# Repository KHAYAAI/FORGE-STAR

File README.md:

# FORGE STAR

**Africa's sovereign satellite data network.** Locally owned low-Earth-orbit (LEO) infrastructure that connects the assets, vessels and people that terrestrial networks will never reach. Data is landed and hosted in South Africa.

FORGE STAR starts with satellite IoT, maritime AIS and sovereign data relay, not consumer broadband. It runs as a ground and services company first (revenue before orbit), then becomes a satellite operator. It's part of the FORGE ecosystem (MYFORGE PTY LTD).

> All figures are illustrative. Regulatory, market and vendor facts need confirming before external use (see [`docs/verification/VERIFY.md`](docs/verification/VERIFY.md)). Not financial advice.

---

## Start here: documents

| Document | For | What it is |
|---|---|---|
| **[Technical and investor brief (PDF)](output/FORGE_STAR_Brief.pdf)** | Investors, counsel, engineers, partners, due diligence | One brief with a section for each reader: case, market, financials, regulation, architecture, RF design, flight software, ground platform, hardware plan, evidence, path to launch, risks, where FORGE STAR reaches (global coverage map, first export markets), sources |
| [Strategy (PDF)](output/FORGE_STAR_Strategy.pdf) · [source](docs/strategy.md) | Founders, board | The full strategy with every analysis check |
| [Launch readiness](docs/LAUNCH_READINESS.md) | Everyone | Scorecard, TRL, critical path, blockers (generated) |
| [Verification register](docs/verification/VERIFY.md) | Counsel, engineers | Every claim, vendor figure and radio value still to confirm, with sources |
| [ITU filing parameters](docs/itu/FILING_PARAMETERS.md) | Spectrum counsel | Draft NGSO filing sheet generated from the design |
| [Mission operations](docs/operations/mission-ops.md) · [Security and POPIA](docs/operations/security.md) | Operations, security | Procedures and controls |

Both PDFs are built from markdown in `docs/`:

```bash
python3 scripts/build_pdf.py                                        # strategy
python3 scripts/build_pdf.py --src docs/brief.md --out output/FORGE_STAR_Brief.pdf \
  --subtitle "Technical and investor brief" --label "Brief v1.2  ·  November 2026  ·  Confidential"
```

---

## The platform in one picture

```mermaid
flowchart LR
    subgraph Field["In the field"]
        D["Devices<br/>mine pumps, farm sensors,<br/>collars, vessels, trackers"]
    end
    subgraph Space["Space segment"]
        S["FORGE STAR satellites<br/>F´ flight software + libforge<br/>store-and-forward buffer"]
    end
    subgraph Ground["Ground segment (SA)"]
        G["Gateways<br/>Hartebeesthoek, Cape Town + partners<br/>FEC decode, dedupe, acks"]
        K[("Kafka")]
        DB[("TimescaleDB<br/>hosted in SA")]
    end
    subgraph Customers["Customers"]
        TB["ThingsBoard<br/>dashboards"]
        API["Customer API<br/>devices, messages, SLA, usage"]
    end
    R["Resale partner<br/>(Stage 0, before our satellites)"]

    D -- "NB-IoT NTN uplink<br/>(re-sent until acked)" --> S
    S -- "X-band downlink<br/>RS(255,223) CCSDS" --> G
    G -- "ACK frames" --> S
    S -. "acks relayed" .-> D
    D -. "Stage 0" .-> R --> K
    G --> K --> DB
    DB --> TB
    DB --> API
```

**How a message travels:**
1. A device sends a reading. Every FORGE STAR satellite overhead takes a copy and holds it on board.
2. When a satellite passes over a gateway, it sends its stored messages down in error-corrected link blocks.
3. The gateway decodes them, removes duplicate copies and records each message. It then sends acknowledgements back up.
4. Satellites relay the acknowledgements, so devices stop re-sending and satellites drop copies they no longer need.
5. Messages flow through Kafka into TimescaleDB, hosted in South Africa. Customers see them in ThingsBoard dashboards and through the API.

In **Stage 0**, before our own satellites fly, the same platform carries traffic from a resale partner. Customers get the same dashboards and API, then move onto our satellites with no change on their side.

---

## What's in this repository

| Layer | What it does | Where |
|---|---|---|
| **Flight software** | NASA F´ deployment (`Payload`): store-and-forward, signed-command authentication, safe mode, onboard pass prediction, persistence. Runs on x86 and 64-bit ARM. | [`flight/fprime/`](flight/fprime) |
| **Flight core** | Portable C99, no dynamic memory: store-and-forward buffer (CRC-checked, survives reboot), frames, acks, Reed–Solomon, HMAC command auth, pass predictor. Byte-identical to the ground code. | [`flight/libforge/`](flight/libforge) |
| **Device SDK** | C99 library for customer devices: queue, re-send until acked, expiry | [`flight/libforge/include/forge_device.h`](flight/libforge/include/forge_device.h) |
| **Mission operations** | Signed commanding and telemetry/event decoding for the flight software; procedures | [`ground/ops/`](ground/ops), [`docs/operations/`](docs/operations) |
| **Software modem** | BPSK receive chain from IQ samples (Doppler, timing, phase) with CCSDS convolutional coding + Viterbi | [`forgestar/modem.py`](forgestar/modem.py), [`forgestar/conv.py`](forgestar/conv.py) |
| **Billing** | Monthly invoices per active device with SLA credits | [`ground/billing/`](ground/billing) |
| **ITU filing sheet** | Draft NGSO filing parameters generated from the design | [`docs/itu/`](docs/itu) |
| **Link layer** | RS(255,223) with CCSDS parameters and dual basis, CCSDS randomiser, sync marker. Corrects up to 16 bad bytes per block. | [`forgestar/fec.py`](forgestar/fec.py) |
| **Frames** | Store-and-forward data frames and ACK frames shared by satellite and ground | [`forgestar/frames.py`](forgestar/frames.py) |
| **Gateway** | Decodes downlinks (Kafka, capture files, SatNOGS Network), removes duplicates, sends acks | [`ground/gateway/`](ground/gateway) |
| **Data platform** | Kafka → TimescaleDB, ingest, delivery-time (SLA) views | [`ground/`](ground) |
| **Dashboards** | ThingsBoard provisioning: devices plus an operations dashboard | [`ground/thingsboard/`](ground/thingsboard) |
| **Customer API** | FastAPI with per-customer keys: devices, messages, SLA, monthly usage; rate limits, audit log, metrics | [`ground/api/`](ground/api) |
| **Production deployment** | TLS, backups, no exposed data ports, required secrets | [`ground/deploy/`](ground/deploy) |
| **Simulated space segment** | Runs a constellation on a sped-up clock, so the whole platform can be tested without satellites | [`ground/sandf/`](ground/sandf) |
| **Constellation design** | Orbits with J2 (checked against SGP4), coverage, link budget, antenna options, delivery time | [`sim/`](sim), [`forgestar/`](forgestar) |
| **Hardware** | Circuit boards as code. Two boards placed and autorouted with every connection made and a clean KiCad design check: the payload interface board and an IoT test device. Written in Zener (Diode's open-source `pcb` tool) and SKiDL. Not yet reviewed by an engineer or built. | [`hardware/zener/`](hardware/zener), [`hardware/`](hardware) |
| **3D models** | Concept models of the demonstrator (6U), the operational IoT satellite (12U) and a broadband satellite, plus both boards. STEP and GLB files. | [`hardware/3d/`](hardware/3d) |
| **Capacity model** | Messages per satellite per pass, and how many devices a fleet can carry | [`forgestar/capacity.py`](forgestar/capacity.py), [`sim/capacity_study.py`](sim/capacity_study.py) |
| **Business** | Financial model (Stages 0–3, stress scenarios, monthly cash, 30% ownership check) | [`model/`](model) |
| **Readiness** | 40 outside milestones (ICASA/ITU, funding, partners, customers), TRL tracking, launch readiness report | [`readiness/`](readiness), [`docs/LAUNCH_READINESS.md`](docs/LAUNCH_READINESS.md) |
| **Strategy** | The full strategy; the PDF is built from it | [`docs/strategy.md`](docs/strategy.md), [`output/`](output) |

---

## Run it

**Prerequisites:** Docker, Python 3.11+, a C compiler. For the flight software you also need CMake and F´'s tools; for hardware, KiCad 7+.

```bash
git clone --recurse-submodules https://github.com/KHAYAAI/FORGE-STAR.git
cd FORGE-STAR
pip install -r requirements.txt
```

**The platform** (simulated devices and the Stage 3 constellation of 48 satellites and 6 gateways, gateway, database, API):

```bash
cd ground && docker compose up -d
```

Then:
- **Customer API docs:** http://localhost:8000/docs (create a key with `docker compose exec api python app.py create-key "FORGE Freight"`)
- **Delivery times:** `docker compose exec timescaledb psql -U forge -d forgestar -c "select * from latency_sla;"`
- **With ThingsBoard** (needs about 2 GB of RAM): `docker compose --profile full up -d`, then `python3 thingsboard/provision.py`, and open http://localhost:8080 (`tenant@thingsboard.org` / `tenant`)

**Flight software:**

```bash
cd flight/fprime && pip install -r fprime/requirements.txt
fprime-util generate && fprime-util build && fprime-util check     # build + unit tests
cd ../.. && python3 flight/run_payload.py                           # run it, decode its downlink on the ground
```

Command it (signed) from the ground: `python3 ground/ops/forge_ops.py --dict flight/fprime/build-artifacts/Linux/Payload/dict/PayloadTopologyDictionary.json --port 50000 --key <hex> --cmd Payload.cmdDisp.CMD_NO_OP`, then start the flight binary with `FORGE_CMD_KEY=<hex>` and `-a 127.0.0.1 -p 50000`.

For 64-bit ARM, use `fprime-util generate aarch64-linux && fprime-util build aarch64-linux`, then `python3 flight/run_payload.py --arch aarch64` (runs under QEMU).

**Analysis and documents:**

```bash
python3 sim/equatorial_study.py          # Stage 3 constellation and gateway design
python3 sim/antenna_trade.py             # payload antenna options, with gain tied to beam shape
python3 sim/capacity_study.py            # messages per pass and per device per day
python3 sim/coverage_map.py [--stage4]   # global coverage map -> docs/img/coverage-stage3.png
python3 model/financial_model.py         # financial model and stress tests
python3 scripts/launch_readiness.py      # docs/LAUNCH_READINESS.md
python3 scripts/build_pdf.py             # output/FORGE_STAR_Strategy.pdf
python3 -m pytest                        # test suite
```

CI runs all of this on every push: the Python tests and analysis, the platform image builds, the flight software (C core, F´ unit tests, native and ARM runs), and the hardware pipeline.

---

## Key numbers (illustrative)

| Item | Value |
|---|---|
| **Stage 3 constellation** | 42 satellites at 45° + 6 at 10° (48), 550 km |
| **Gateways** | Hartebeesthoek, Cape Town, Walvis Bay, Mauritius, Malindi, Lagos |
| **Delivery target (design)** | 95% of messages within 26 minutes at all 7 modelled customer sites |
| **Delivery measured (live run)** | 95% within ~40 minutes on 24 satellites with SA gateways only |
| **Year-6 revenue** | $37.5M base; $31.6M with IoT at ~$1/device; $19.5M without a government contract |
| **Equity to Stage 3** | ~$50M |
| **Delivery measured on the Stage 3 design (live run)** | 95% of satellite messages within 9 minutes |
| **Link margin** | Decodes at Eb/N0 ≈ 2.5 dB with CCSDS RS + convolutional coding |
| **First payload in orbit** | ~Feb 2029 on the fast track (hosted payload); ~May 2028 if everything runs in parallel with money up front; own satellite ~Jun 2029 |
| **Service antenna** | Isoflux, ~8 W RF: devices reach a satellite from 16° elevation. Needs ~38 W from the bus during passes (a 12U) |
| **Demonstrator antenna** | Simple patch: 47° elevation (34° with deep coverage mode). Poor coverage by design |
| **Capacity** | ~6 messages a second per NB-IoT carrier per satellite. Stage 3 carries ~1.4 messages per device per day at 330,000 devices |
| **Year-6 EBITDA** | $11.3M base (our satellites carry ~42% of IoT devices, the rest stay on the resale partner); $12.6M with a compact protocol of our own |

## Hardware: build, buy, bridge

Boards are written as code and checked with KiCad. The two current boards live in [`hardware/zener/`](hardware/zener), with fabrication files for review in each board's `fab/` folder; [heypcb.ai](https://heypcb.ai) remains an option for later boards. GitHub CI autoroutes the boards with Freerouting (`.github/workflows/route-boards.yml`). The gaps heypcb.ai does not cover are bridged with flight-heritage suppliers and mature tools: hosted-payload platforms or the bus partner for structure, thermal and integration; flight-heritage S/X-band radios; Antenna Magus and openEMS for antennas; SPENVIS and iThemba LABS (Cape Town) for radiation. Details, list prices and what still needs a quote are in section 09 of the brief and items V1–V7 of the verification register.

## Status

**Updated November 2026.** An independent review found the first antenna figures too optimistic. The link budget now ties antenna gain to beam shape, the simulations use the downlink limit, and the financial model is tied to fleet capacity.

The software and ground platform are at TRL 4–5. Everything that can be built without hardware is in place; the remaining software (payload radio base station, real drivers, bus integration) needs the lab kit and bus partner. Payload hardware, the bus partner, spectrum licensing, funding and customers are the work still ahead. See [`docs/LAUNCH_READINESS.md`](docs/LAUNCH_READINESS.md) for the scorecard, critical path and blockers.

Project context for Claude Code is in [`CLAUDE.md`](CLAUDE.md).

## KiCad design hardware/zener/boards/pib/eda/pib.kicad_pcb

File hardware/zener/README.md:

# FORGE STAR boards in Zener (trial)

A trial of [Diode's Zener language and `pcb` tool](https://github.com/diodeinc/pcb) (MIT licence) next to the
existing SKiDL pipeline in `hardware/boards/`. Boards are written as code; `pcb` checks them and produces KiCad files.

All designs here are first drafts with illustrative values. An electrical engineer must review them before fabrication.

| Board | File | What it is | Status |
|---|---|---|---|
| Payload interface board (PIB) | `boards/pib/pib.zen` | Port of the SKiDL board: MCU, CAN to the bus, radio power switch, telemetry | Builds, 35 components |
| IoT test device | `boards/iot_node/iot_node.zen` | Battery NB-IoT node with GNSS for the lab test-bed and field trials | Builds, 71 components |

## Use

```bash
curl -fsSL https://raw.githubusercontent.com/diodeinc/pcb/main/install.sh | bash   # installs pcb
cd hardware/zener
pcb build boards/pib/pib.zen                  # check the design
pcb build boards/iot_node/iot_node.zen
pcb bom --offline boards/iot_node/iot_node.zen   # parts list, nothing sent to Diode
pcb layout --no-open boards/pib/pib.zen       # KiCad board file (needs KiCad 10)
```

`pcb bom` without `--offline`, `pcb quote` and `pcb auth` send design data to Diode's servers. Do not use them
until an NDA and an export-control check are in place.

## Parts

Each board keeps its own symbols and footprints in `parts/`. Add one from the installed KiCad libraries with:

```bash
python3 tools/import_kicad_part.py boards/iot_node RF_GSM:BC66
```

## Layout

```bash
pcb layout --no-open boards/iot_node/iot_node.zen   # creates or updates the KiCad board (needs KiCad 10)
python3 tools/place.py boards/iot_node              # positions from placement.json, outline, ground pours
FREEROUTING_JAR=... python3 tools/route.py boards/iot_node   # autoroute + ground stitching (runs in GitHub CI)
```

| Board | Size | Placement | Routing |
|---|---|---|---|
| Payload interface board | 58 x 40 mm, 4 layers | Done | Done: every connection made, KiCad design check reports 0 errors |
| IoT test device | 84 x 45 mm, 4 layers | Done | Done: every connection made, KiCad design check reports 0 errors |

Both boards have four grounded M2.5 mounting holes and three fiducials.

Gerber, drill and placement files are in each board's `fab/` folder. They are for review, not yet for ordering.

3D pictures are in `docs/img/` (`pib-3d.png`, `iot_node-3d.png`) and 3D STEP files sit next to each board.
Several chips show as bare pads because KiCad's 3D model library is not installed here.

## Datasheet checks done (from public sources, November 2026)

| Item | Finding | Result in the design |
|---|---|---|
| MAX-M10S `VIO_SEL` | u-blox: connect to GND for 1.8 V, leave open for 3.3 V | Tied to GND. Correct for 1.8 V. |
| MAX-M10S supply | 1.76 V to 1.98 V in 1.8 V mode | The 1.8 V regulator's tolerance leaves little margin at the low end. Consider a tighter regulator. |
| BC66 `PWRKEY` | Thresholds are relative to VBAT; Quectel recommends an open-drain or open-collector driver | Driven by an open-collector transistor. Matches. |
| BC66 `RESET`, `PSM_EINT` | Active low | Driven the same way. The voltage domain of `PSM_EINT` was not found; the transistor makes it safe either way. |
| BC66 pin numbers | PWRKEY 7, RESET 15, PSM_EINT 19 | Match the KiCad symbol. |
| CC660D-LS (satellite module) | Same 17.7 x 15.8 x 2.0 mm LCC+LGA outline as BC66; has PWRKEY, PSM_EINT, UART, USIM, ADC; needs an external GNSS module | Outline and interfaces fit, and the board already has GNSS. **The pin-by-pin map is still unconfirmed**: Quectel's CC660D-LS hardware design manual is needed. |
| BC660K-GL (same footprint family) | No PWRKEY; adds BOOT and VIO_SEL; do not pull MAIN_RXD up to VDD_EXT | Not a drop-in for this board without changes. |

## Open items before fabrication

- **Autorouted, not reviewed.** Routing was done by Freerouting in CI (`.github/workflows/route-boards.yml`). Power traces use the default width, decoupling and RF traces are not hand-placed, and silkscreen has cosmetic warnings.
- **CC660D-LS pin map:** get the hardware design manual from Quectel and compare every pin.
- **RF:** antenna traces need 50 ohm controlled impedance; the matching network values are placeholders that need
  measurement on a network analyser.
- **Engineer review:** an electrical engineer must review schematic, placement and routing. The checks above are
  from public datasheet summaries, not a substitute for that review.

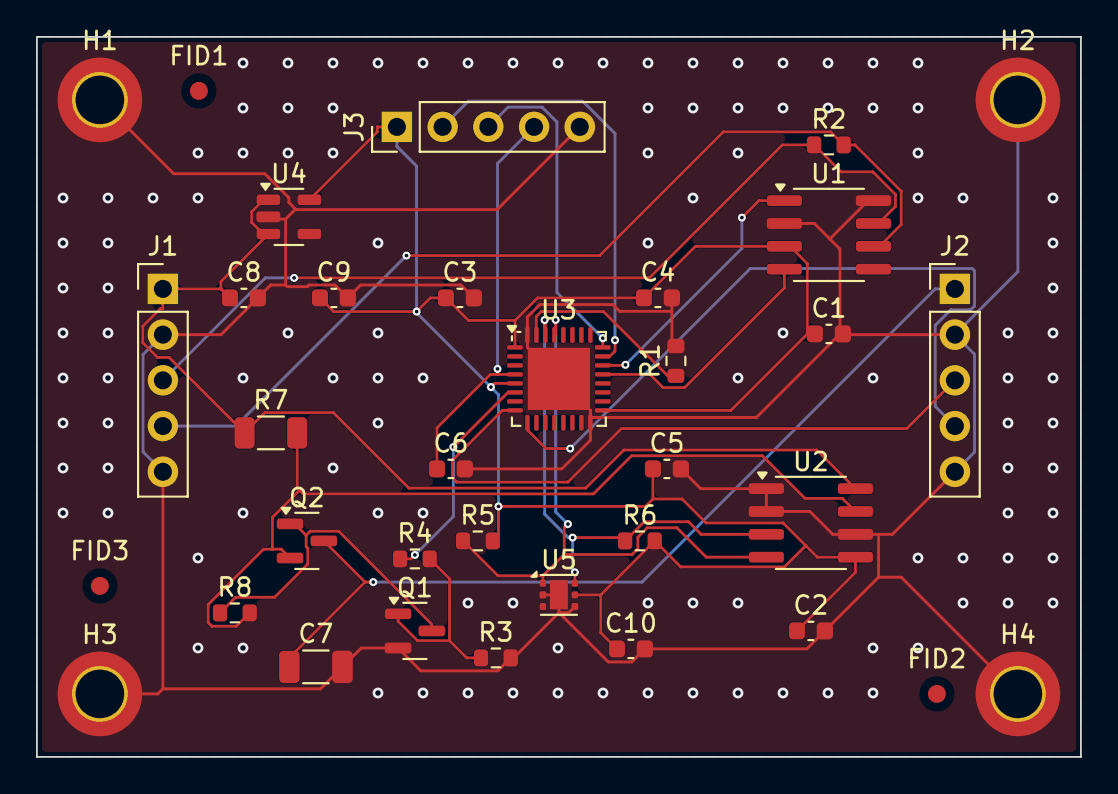
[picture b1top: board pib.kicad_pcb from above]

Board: 4 copper layers, 58.0 x 40.0 mm, 35 parts (0 on the bottom side), 20 nets.

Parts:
C1, C2, C3, C4, C10: 100nF 6.3V; C_0603_1608Metric
C5: 4.7uF 6.3V; C_0603_1608Metric
C6: 100nF; C_0603_1608Metric
C7: 10uF 10V; C_1206_3216Metric
C8: 1uF 10V; C_0603_1608Metric
C9: 1uF 6.3V; C_0603_1608Metric
FID1, FID2, FID3: Fiducial; Fiducial_1mm_Mask2mm
H1, H2, H3, H4: M2.5 DIN965 TopBottom; MountingHole_2.7mm_M2.5_DIN965_Pad_TopBottom
J1, J2, J3: 2.54mm 5 x 1 THT Vertical Male; PinHeader_1x05_P2.54mm_Vertical
Q1: 2N7002; SOT-23
Q2: AO3401A; SOT-23
R1: 10k; R_0603_1608Metric
R2: 120; R_0603_1608Metric
R3, R8: 100k; R_0603_1608Metric
R4: 100; R_0603_1608Metric
R5, R6: 4.7k; R_0603_1608Metric
R7: 50m; R_1206_3216Metric
U1: SN65HVD230DR; SOIC-8_3.9x4.9mm_P1.27mm
U2: INA219AIDR; SOIC-8_3.9x4.9mm_P1.27mm
U3: STM32L432KCU6; QFN-32-1EP_5x5mm_P0.5mm_EP3.45x3.45mm
U4: AP2112K-3.3TRG1; SOT-23-5
U5: TMP117AIDRVR; WSON-6-1EP_2x2mm_P0.65mm_EP1x1.6mm

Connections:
+3V3: C1.1, C2.1, C3.1, C4.1, C5.1, C9.1, C10.1, J3.1, R5.2, R6.2, U1.3, U2.5, U3.1, U3.5, U3.17, U4.5, U5.5
BOOT0: R1.1, U3.31
CANH: J1.3, R2.1, U1.7
CANL: J1.4, R2.2, U1.6
CAN_RX: U1.4, U3.21
CAN_TX: U1.1, U3.22
DRV_GATE: Q1.1, R3.1, R4.2
GND: C1.2, C2.2, C3.2, C4.2, C5.2, C6.2, C7.2, C8.2, C9.2, C10.2, H1.1, H2.1, H3.1, H4.1, J1.2, J1.5, J2.2, J2.5, J3.5, Q1.2, R1.2, R3.2, U1.2, U1.8, U2.1, U2.2, U2.6, U3.16, U3.32, U3.33, U4.2, U5.2, U5.4, U5.7
I2C_SCL: R5.1, U2.4, U3.29, U5.1
I2C_SDA: R6.1, U2.3, U3.30, U5.6
NRST: C6.1, J3.4, U3.4
RADIO_EN: R4.1, U3.6
RADIO_PWR: C7.1, J2.1, Q2.3
SWCLK: J3.3, U3.24
SWDIO: J3.2, U3.23
SW_GATE: Q1.3, Q2.1, R8.1
UART_RX: J2.4, U3.9
UART_TX: J2.3, U3.8
VIN: C8.1, J1.1, R7.1, U2.8, U4.1, U4.3
VIN_SENSE: Q2.2, R7.2, R8.2, U2.7

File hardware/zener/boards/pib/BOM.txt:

Legend:
 ■  Plenty available / easy to source         ■  House component       
 ■  Limited inventory / harder to source      ■  DNP (Do Not Populate) 
 ■  Insufficient stock / hard to source                                
┌──────┬─────────────────┬─────────────────┬─────────────────────────────┬─────────────────────────────────┬────────────────────────────────┐
│ Qty  ┆ Designators     ┆ MPN             ┆ Manufacturer                ┆ Package                         ┆ Description                    │
╞══════╪═════════════════╪═════════════════╪═════════════════════════════╪═════════════════════════════════╪════════════════════════════════╡
│    5 ┆ C1,C2,C3,C4,C10 ┆                 ┆                             ┆ 0603                            ┆ 100nF 6.3V                     │
│    1 ┆ C5              ┆                 ┆                             ┆ 0603                            ┆ 4.7uF 6.3V                     │
│    1 ┆ C6              ┆                 ┆                             ┆ 0603                            ┆ 100nF                          │
│    1 ┆ C7              ┆                 ┆                             ┆ 1206                            ┆ 10uF 10V                       │
│    1 ┆ C8              ┆                 ┆                             ┆ 0603                            ┆ 1uF 10V                        │
│    1 ┆ C9              ┆                 ┆                             ┆ 0603                            ┆ 1uF 6.3V                       │
│    3 ┆ J1,J2,J3        ┆                 ┆                             ┆ PinHeader_1x05_P2.54mm_Vertical ┆ 2.54mm 5 x 1 THT Vertical Male │
│    1 ┆ Q1              ┆ 2N7002          ┆ onsemi                      ┆                                 ┆                                │
│    1 ┆ Q2              ┆ AO3401A         ┆ Alpha & Omega Semiconductor ┆                                 ┆                                │
│    1 ┆ R1              ┆                 ┆                             ┆ 0603                            ┆ 10k                            │
│    1 ┆ R2              ┆                 ┆                             ┆ 0603                            ┆ 120                            │
│    2 ┆ R3,R8           ┆                 ┆                             ┆ 0603                            ┆ 100k                           │
│    1 ┆ R4              ┆                 ┆                             ┆ 0603                            ┆ 100                            │
│    2 ┆ R5,R6           ┆                 ┆                             ┆ 0603                            ┆ 4.7k                           │
│    1 ┆ R7              ┆                 ┆                             ┆ 1206                            ┆ 50m                            │
│    1 ┆ U1              ┆ SN65HVD230DR    ┆ Texas Instruments           ┆                                 ┆                                │
│    1 ┆ U2              ┆ INA219AIDR      ┆ Texas Instruments           ┆                                 ┆                                │
│    1 ┆ U3              ┆ STM32L432KCU6   ┆ STMicroelectronics          ┆                                 ┆                                │
│    1 ┆ U4              ┆ AP2112K-3.3TRG1 ┆ Diodes Incorporated         ┆                                 ┆                                │
│    1 ┆ U5              ┆ TMP117AIDRVR    ┆ Texas Instruments           ┆                                 ┆                                │
└──────┴─────────────────┴─────────────────┴─────────────────────────────┴─────────────────────────────────┴────────────────────────────────┘

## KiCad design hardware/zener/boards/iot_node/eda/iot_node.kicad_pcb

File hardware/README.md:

# FORGE STAR hardware: in-house PCB pipeline

An open-source replacement for an AI PCB service such as heypcb.ai. Boards are written as code,
checked automatically and turned into fab files on every push.

```
circuit as code (SKiDL, KiCad symbol libraries)      hardware/boards/<board>/<board>.py
   │  electrical rule check (ERC) + netlist
   ▼
placement + rules (KiCad pcbnew Python API)          hardware/tools/forge_pcb.py
   │  autoroute (Freerouting, opt-in)
   ▼
ground pours + design rule check (DRC)
   │
fab package: Gerbers, drill, pick-and-place, BOM, SVG   hardware/build/<board>/<board>-fab.zip
```

## Run

```bash
sudo apt-get install kicad kicad-symbols kicad-footprints      # KiCad 7+
pip install --no-deps skidl graphviz simp_sexp
python3 hardware/boards/pib/pib.py                               # ERC, netlist, placed PCB, DRC, fab files
FREEROUTING_JAR=/path/to/freerouting-1.9.0.jar python3 hardware/boards/pib/pib.py   # + autoroute
```

## Boards

| Board | What | Status |
|---|---|---|
| `pib` payload interface board rev A | STM32L432 running libforge, CAN to bus, radio power switch, INA219 current, TMP117 temperature, SWD | ERC clean (0 errors); placed; DRC 0 blocking issues before routing; not yet autorouted |

## What each open-source tool replaces

| heypcb.ai feature | Open-source equivalent here | Notes |
|---|---|---|
| Describe a circuit, get a schematic | **SKiDL** (Python) or **atopile** (declarative); Claude Code writes the code | Circuits are reviewable diffs, testable in CI |
| Component library | **KiCad symbol/footprint libraries** (10k+ parts) | Add JLCPCB/LCSC parts with `kicad-jlcpcb-tools` |
| "Circuit World" of open boards to fork | **LibreCube, OreSat, PyCubed, BIRDS** (all KiCad, open hardware) | Fork proven CubeSat boards instead of starting blank |
| Placement | `forge_pcb.py` (anchor ICs, auto-place passives near their IC) | Good enough for low-speed boards; RF boards still need hand placement |
| Autorouting | **Freerouting** | Fine for digital/power boards; RF and high-speed routed by hand |
| Design checks | KiCad **ERC/DRC** (scripted) | Blocking vs review categories in the DRC summary |
| Gerbers, BOM, pick-and-place | **kicad-cli** (+ KiBot for richer outputs) | Zip ready for JLCPCB, PCBWay or an SA fab |
| Simulation | **ngspice** (circuits), **openEMS** (antennas, RF) | openEMS covers the patch/isoflux antenna work |
| Mechanical fit | **FreeCAD** + KiCad StepUp | Check board against the CubeSat frame |

What neither heypcb nor this pipeline does: radiation qualification, thermal design, RF tuning on a vector network analyser, and bus integration. Those stay with the engineers and the bus partner.

## Zener trial

`hardware/zener/` holds a trial of Diode's Zener language and `pcb` tool: the payload interface board ported from SKiDL, and a new IoT test device. See [`zener/README.md`](zener/README.md).

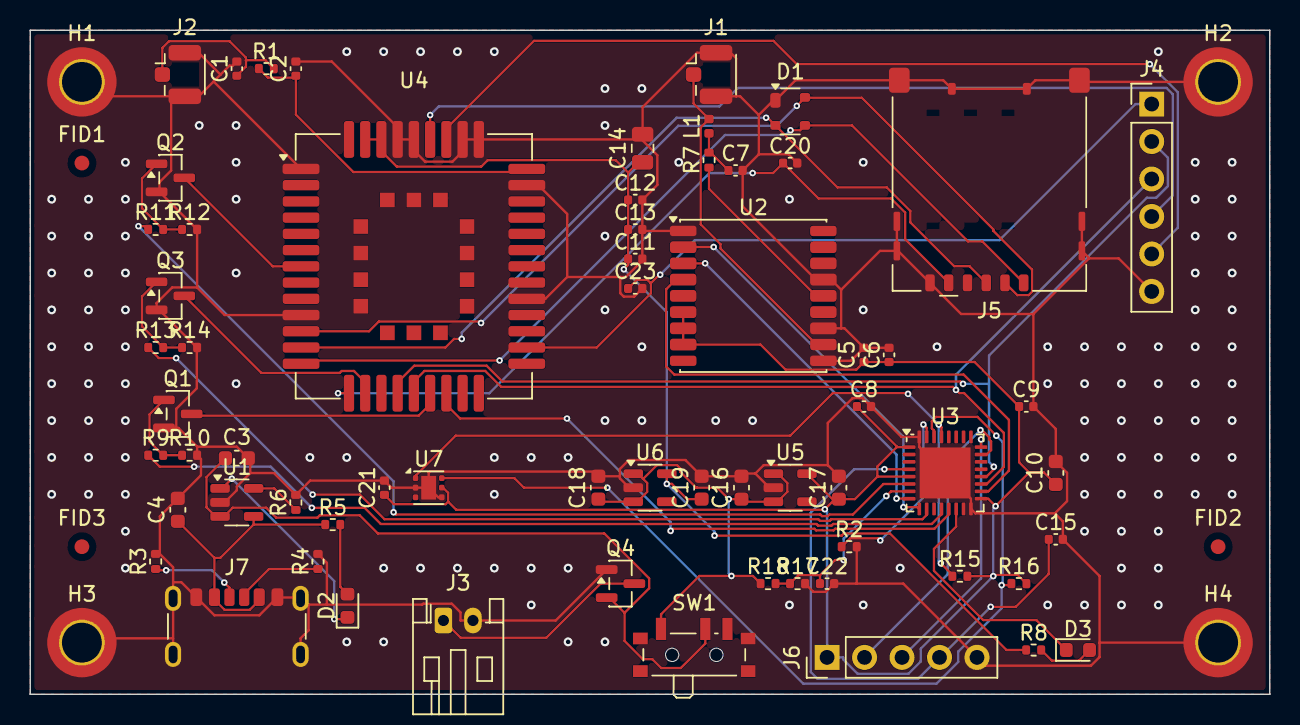
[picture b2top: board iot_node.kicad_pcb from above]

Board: 4 copper layers, 84.0 x 45.0 mm, 71 parts (0 on the bottom side), 48 nets.

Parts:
C1, C2: 1pF; C_0402_1005Metric
C3, C10: 4.7uF 6.3V; C_0603_1608Metric
C4: 4.7uF 10V; C_0603_1608Metric
C5, C8, C9, C12, C20, C21, C23: 100nF 6.3V; C_0402_1005Metric
C6: 1uF 6.3V; C_0402_1005Metric
C7: 10nF; C_0402_1005Metric
C11: 22pF 6.3V; C_0402_1005Metric
C13: 100pF 6.3V; C_0402_1005Metric
C14: 22uF 6.3V; C_0805_2012Metric
C15, C22: 100nF; C_0402_1005Metric
C16, C17, C18, C19: 1uF 6.3V; C_0603_1608Metric
D1: SP0503BAHTG; SOT-143
D2: LED ORANGE; LED_0603_1608Metric
D3: LED RED; LED_0603_1608Metric
FID1, FID2, FID3: Fiducial; Fiducial_1mm_Mask2mm
H1, H2, H3, H4: M2.5 DIN965 TopBottom; MountingHole_2.7mm_M2.5_DIN965_Pad_TopBottom
J1, J2: U.FL-R-SMT-1(10); U.FL_Hirose_U.FL-R-SMT-1_Vertical
J3: S2B-PH-K-S; JST_PH_S2B-PH-K_1x02_P2.00mm_Horizontal
J4: 2.54mm 6 x 1 THT Vertical Male; PinHeader_1x06_P2.54mm_Vertical
J5: SF53S006VCBR2000; microSIM_JAE_SF53S006VCBR2000
J6: 2.54mm 5 x 1 THT Vertical Male; PinHeader_1x05_P2.54mm_Vertical
J7: USB4125-GF-A; USB_C_Receptacle_GCT_USB4125-xx-x_6P_TopMnt_Horizontal
L1: 27nH; L_0402_1005Metric
Q1, Q2, Q3: MMBT3904; SOT-23
Q4: AO3401A; SOT-23
R1: 0; R_0402_1005Metric
R2: 10k; R_0402_1005Metric
R3, R4: 5.1k; R_0402_1005Metric
R5, R8: 1k; R_0402_1005Metric
R6: 2k; R_0402_1005Metric
R7: 10; R_0402_1005Metric
R9, R11, R13, R15, R16: 4.7k; R_0402_1005Metric
R10, R12, R14: 47k; R_0402_1005Metric
R17: 470k; R_0402_1005Metric
R18: 1M; R_0402_1005Metric
SW1: PCM12SMTR; SW_SPDT_PCM12
U1: MCP73831T-2ACI/OT; SOT-23-5
U2: MAX-M10S-00B; ublox_MAX
U3: STM32L432KCU6; QFN-32-1EP_5x5mm_P0.5mm_EP3.45x3.45mm
U4: BC66NB-04-STD; Quectel_BC66
U5: AP2112K-1.8TRG1; SOT-23-5
U6: AP2112K-3.3TRG1; SOT-23-5
U7: TMP117AIDRVR; WSON-6-1EP_2x2mm_P0.65mm_EP1x1.6mm

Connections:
+1V8: C5.1, C6.1, C8.1, C9.1, C10.1, C17.1, C21.1, J6.1, R15.2, R16.2, U2.6, U2.7, U2.8, U3.1, U3.5, U3.17, U5.5, U7.5
BAT: C3.1, Q4.2, SW1.2, U1.3
BAT_RAW: J3.1, Q4.3
BOOT0: R2.1, U3.31
CC1: J7.A5, R3.1
CC2: J7.B5, R4.1
CHG_LED: D2.2, R5.2
CHG_PROG: R6.1, U1.5
CHG_STAT: D2.1, U1.1
DBG_RXD: J4.5, U4.38
DBG_TXD: J4.4, U4.39
GND: C1.2, C2.2, C3.2, C4.2, C5.2, C6.2, C7.2, C8.2, C9.2, C10.2, C11.2, C12.2, C13.2, C14.2, C15.2, C16.2, C17.2, C18.2, C19.2, C20.2, C21.2, C22.2, C23.2, D1.1, H1.1, H2.1, H3.1, H4.1, J1.2, J2.2, J3.2, J4.6, J5.5, J5.SH, J6.5, J7.A12, J7.B12, J7.S1, Q1.2, Q2.2, Q3.2, Q4.1, R2.2, R3.2, R4.2, R6.2, R10.2, R12.2, R14.2, R17.2, U1.2, U2.1, U2.10, U2.12, U2.15, U3.16, U3.32, U3.33, U4.1, U4.10, U4.27, U4.34, U4.36, U4.37, U4.40, U4.41, U5.2, U6.2, U7.2, U7.4, U7.7
GNSS_BIAS: C7.1, L1.1, R7.2
GNSS_PPS: U2.4, U3.18
GNSS_RF: J1.1, L1.2, U2.11
GNSS_RXD: U2.3, U3.8
GNSS_TXD: U2.2, U3.9
GNSS_VRF: R7.1, U2.14
I2C_SCL: R15.1, U3.29, U7.1
I2C_SDA: R16.1, U3.30, U7.6
LED_A: D3.2, R8.2
LED_K: D3.1, U3.14
MOD_RESET: Q3.3, U4.15
MOD_RI: U3.13, U4.20
MOD_RXD: J4.3, U3.19, U4.18
MOD_TXD: J4.2, U3.20, U4.17
NRST: C15.1, J6.4, U3.4
PSM_B: Q1.1, R9.2, R10.1
PSM_CTL: R9.1, U3.12
PSM_EINT: Q1.3, U4.19
PWRKEY: Q2.3, U4.7
PWRKEY_B: Q2.1, R11.2, R12.1
PWRKEY_CTL: R11.1, U3.6
RESET_B: Q3.1, R13.2, R14.1
RESET_CTL: R13.1, U3.10
RF_ANT: C1.1, J2.1, R1.2
RF_MOD: C2.1, R1.1, U4.35
SIM_CLK: D1.3, J5.3, U4.13
SIM_DATA: D1.4, J5.7, U4.11
SIM_RST: D1.2, J5.2, U4.12
SIM_VDD: C20.1, J5.1, U4.14
SWCLK: J6.3, U3.24
SWDIO: J6.2, U3.23
VBAT_SENSE: C22.1, R17.1, R18.2, U3.7
VBUS: C4.1, J7.A9, J7.B9, R5.1, U1.4
VDD_EXT: C23.1, J4.1, U4.24
VSYS: C16.1, C18.1, R18.1, SW1.1, U5.1, U5.3, U6.1, U6.3
V_MOD: C11.1, C12.1, C13.1, C14.1, C19.1, R8.1, U4.42, U4.43, U6.5

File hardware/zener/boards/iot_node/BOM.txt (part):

Legend:
 ■  Plenty available / easy to source         ■  House component       
 ■  Limited inventory / harder to source      ■  DNP (Do Not Populate) 
 ■  Insufficient stock / hard to source                                
┌──────┬──────────────────────────┬───────────────────┬─────────────────────────────┬─────────────────────────────────┬─────────────────────────────────────────────────────────────┐
│ Qty  ┆ Designators              ┆ MPN               ┆ Manufacturer                ┆ Package                         ┆ Description                                                 │
╞══════╪══════════════════════════╪═══════════════════╪═════════════════════════════╪═════════════════════════════════╪═════════════════════════════════════════════════════════════╡
│    2 ┆ C3,C10                   ┆                   ┆                             ┆ 0603                            ┆ 4.7uF 6.3V                                                  │
│    1 ┆ C4                       ┆                   ┆                             ┆ 0603                            ┆ 4.7uF 10V                                                   │
│    7 ┆ C5,C8,C9,C12,C20,C21,C23 ┆                   ┆                             ┆ 0402                            ┆ 100nF 6.3V                                                  │
│    1 ┆ C6                       ┆                   ┆                             ┆ 0402                            ┆ 1uF 6.3V                                                    │
│    1 ┆ C7                       ┆                   ┆                             ┆ 0402                            ┆ 10nF                                                        │
│    1 ┆ C11                      ┆                   ┆                             ┆ 0402                            ┆ 22pF 6.3V                                                   │
│    1 ┆ C13                      ┆                   ┆                             ┆ 0402                            ┆ 100pF 6.3V                                                  │
│    1 ┆ C14                      ┆                   ┆                             ┆ 0805                            ┆ 22uF 6.3V                                                   │
│    2 ┆ C15,C22                  ┆                   ┆                             ┆ 0402                            ┆ 100nF                                                       │
│    4 ┆ C16,C17,C18,C19          ┆                   ┆                             ┆ 0603                            ┆ 1uF 6.3V                                                    │
│    1 ┆ D1                       ┆ SP0503BAHTG       ┆ Littelfuse                  ┆                                 ┆ TVS Diode Array, 5.5V Standoff, 3 Channels, SOT-143 package │
│    1 ┆ D2                       ┆                   ┆                             ┆ 0603                            ┆ LED ORANGE                                                  │
│    1 ┆ D3                       ┆                   ┆                             ┆ 0603                            ┆ LED RED                                                     │
│    2 ┆ J1,J2                    ┆ U.FL-R-SMT-1(10)  ┆ Hirose                      ┆                                 ┆                                                             │
│    1 ┆ J3                       ┆ S2B-PH-K-S        ┆ JST                         ┆                                 ┆                                                             │
│    1 ┆ J4                       ┆                   ┆                             ┆ PinHeader_1x06_P2.54mm_Vertical ┆ 2.54mm 6 x 1 THT Vertical Male                              │
│    1 ┆ J5                       ┆ SF53S006VCBR2000  ┆ JAE                         ┆                                 ┆                                                             │
│    1 ┆ J6                       ┆                   ┆                             ┆ PinHeader_1x05_P2.54mm_Vertical ┆ 2.54mm 5 x 1 THT Vertical Male                              │
│    1 ┆ J7                       ┆ USB4125-GF-A      ┆ GCT                         ┆                                 ┆                                                             │
│    1 ┆ L1                       ┆                   ┆                             ┆ 0402                            ┆ 27nH                                                        │
│    3 ┆ Q1,Q2,Q3                 ┆ MMBT3904          ┆ onsemi                      ┆                                 ┆                                                             │
│    1 ┆ Q4                       ┆ AO3401A           ┆ Alpha & Omega Semiconductor ┆                                 ┆ -4.0A Id, -30V Vds, P-Channel MOSFET, SOT-23                │
│    1 ┆ R1                       ┆                   ┆                             ┆ 0402                            ┆ 0                                                           │
│    1 ┆ R2                       ┆                   ┆                             ┆ 0402                            ┆ 10k                                                         │
│    2 ┆ R3,R4                    ┆                   ┆                             ┆ 0402                            ┆ 5.1k                                                        │
│    2 ┆ R5,R8                    ┆                   ┆                             ┆ 0402                            ┆ 1k                                                          │
│    1 ┆ R6                       ┆                   ┆                             ┆ 0402                            ┆ 2k                                                          │
│    1 ┆ R7                       ┆                   ┆                             ┆ 0402                            ┆ 10                                                          │
│    5 ┆ R9,R11,R13,R15,R16       ┆                   ┆                             ┆ 0402                            ┆ 4.7k                                                        │
│    3 ┆ R10,R12,R14              ┆                   ┆                             ┆ 0402                            ┆ 47k                                                         │
│    1 ┆ R17                      ┆                   ┆                             ┆ 0402                            ┆ 470k                                                        │
│    1 ┆ R18                      ┆                   ┆                             ┆ 0402                            ┆ 1M                                                          │
│    1 ┆ SW1                      ┆ PCM12SMTR         ┆ C&K                         ┆                                 ┆ Switch, single pole double throw                            │
│    1 ┆ U1                       ┆ MCP73831T-2ACI/OT ┆ Microchip                   ┆                                 ┆                                                             │
│    1 ┆ U2                       ┆ MAX-M10S-00B      ┆ u-blox                      ┆                                 ┆                                                             │
│    1 ┆ U3                       ┆ STM32L432KCU6     ┆ STMicroelectronics          ┆                                 ┆                                                             │
│    1 ┆ U4                       ┆ BC66NB-04-STD     ┆ Quectel                     ┆                                 ┆                                                             │
│    1 ┆ U5                       ┆ AP2112K-1.8TRG1   ┆ Diodes Incorporated         ┆                                 ┆                                                             │
│    1 ┆ U6                       ┆ AP2112K-3.3TRG1   ┆ Diodes Incorporated         ┆                                 ┆                                                             │
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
